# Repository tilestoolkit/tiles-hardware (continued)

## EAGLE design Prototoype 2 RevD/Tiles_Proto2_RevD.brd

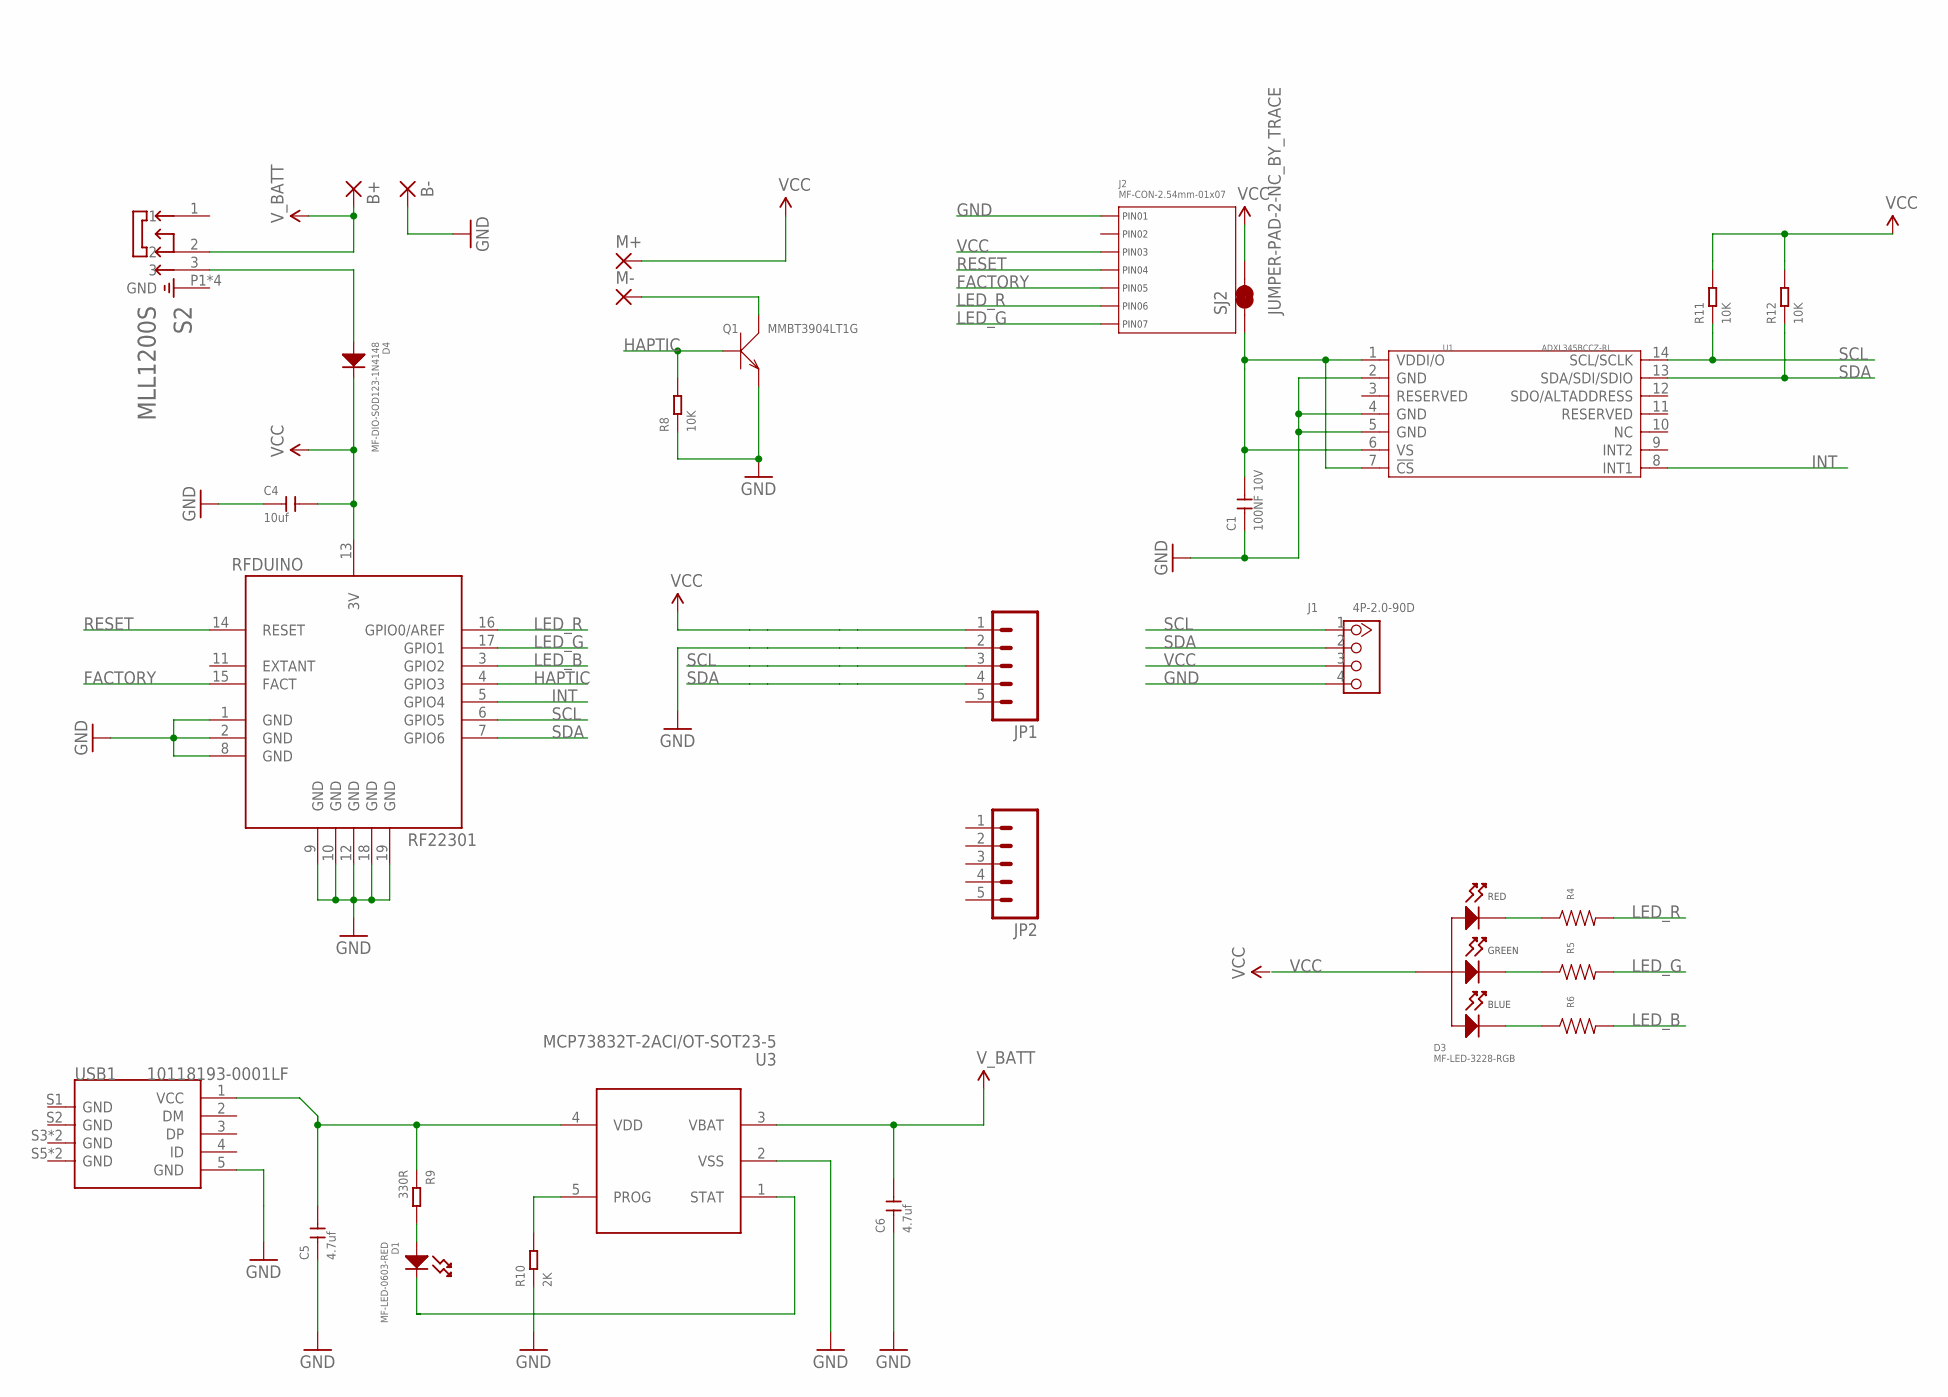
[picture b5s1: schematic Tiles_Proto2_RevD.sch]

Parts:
B+: SMD2; SMD1,27-2,54
B-: SMD2; SMD1,27-2,54
C1: 100NF 10V; C0402
C4: 10uf; C0402
C5, C6: 4.7uf; C0402
D1: MF-LED-0603-RED; LED0603
D3: MF-LED-3228-RGB; PLCC4
D4: MF-DIO-SOD123-1N4148; SOD-123
J1: 4P-2.0-90D; HW4-2.0-90D
J2: MF-CON-2.54mm-01x07; PTH_2.54MM_01X07
JP1, JP2: M05PTH; 1X05
M+: SMD2; SMD1,27-2,54
M-: SMD2; SMD1,27-2,54
Q1: MMBT3904LT1G; SOT-23
R4, R5, R6: RESISTOR_0603; R0603
R8, R11, R12: 10K; R0603
R9: 330R; R0603
R10: 2K; R0603
RFDUINO: RF22301; RFD22301
S2: MLL1200S; SW_MLL1200S
SJ2: JUMPER-PAD-2-NC_BY_TRACE; PAD-JUMPER-2-NC_BY_TRACE_YES_SILK
U1: ADXL345BCCZ-RL; LGA14-0.8-5.0X3.0MM
U3: MCP73832T-2ACI/OT-SOT23-5; SOT-23-5
USB1: 10118193-0001LF; MICRO-USB5+6P-SMD-0.65-B

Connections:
FACTORY: J2.P$5 (PIN5), RFDUINO.15 (FACT)
GND: B-.1, C1.1, C4.1, C5.1, C6.1, J1.4, J2.P$1 (PIN1), JP1.2, Q1.2 (E), R8.1, R10.1, RFDUINO.1 (GND), RFDUINO.2 (GND), RFDUINO.8 (GND), RFDUINO.9 (GND), RFDUINO.10 (GND), RFDUINO.12 (GND), RFDUINO.18 (GND), RFDUINO.19 (GND), S2.P1 (GND), S2.P2 (GND), S2.P3 (GND), S2.P4 (GND), U1.2 (GND), U1.4 (GND), U1.5 (GND), U3.2 (VSS), USB1.5 (GND)
HAPTIC: Q1.1 (B), R8.2, RFDUINO.4 (GPIO3)
INT: RFDUINO.5 (GPIO4), U1.8 (INT1)
LED_B: R6.P$2, RFDUINO.3 (GPIO2)
LED_G: J2.P$7 (PIN7), R5.P$2, RFDUINO.17 (GPIO1)
LED_R: J2.P$6 (PIN6), R4.P$2, RFDUINO.16 (GPIO0/AREF)
unnamed: D3.P$2 (CATHODE_RED), R4.P$1
unnamed: D3.P$3 (CATHODE_GREEN), R5.P$1
unnamed: M-.1, Q1.3 (C)
unnamed: C5.2, R9.1, U3.4 (VDD), USB1.1 (VCC)
unnamed: D4.ANODE, S2.3
unnamed: D1.ANODE, R9.2
unnamed: D1.CATHODE, U3.1 (STAT)
unnamed: R10.2, U3.5 (PROG)
unnamed: D3.P$4 (CATHODE_BLUE), R6.P$1
RESET: J2.P$4 (PIN4), RFDUINO.14 (RESET)
SCL: J1.1, JP1.3, R11.1, RFDUINO.6 (GPIO5), U1.14 (SCL/SCLK)
SDA: J1.2, JP1.4, R12.1, RFDUINO.7 (GPIO6), U1.13 (SDA/SDI/SDIO)
VCC: C4.2, D3.P$1 (ANODE), D4.CATHODE, J1.3, J2.P$3 (PIN3), JP1.1, M+.1, R11.2, R12.2, RFDUINO.13 (3V), SJ2.2
VDDI/O: C1.2, SJ2.1, U1.1 (VDDI/O), U1.6 (VS), U1.7 (!CS)
V_BATT: B+.1, C6.2, S2.2, U3.3 (VBAT)

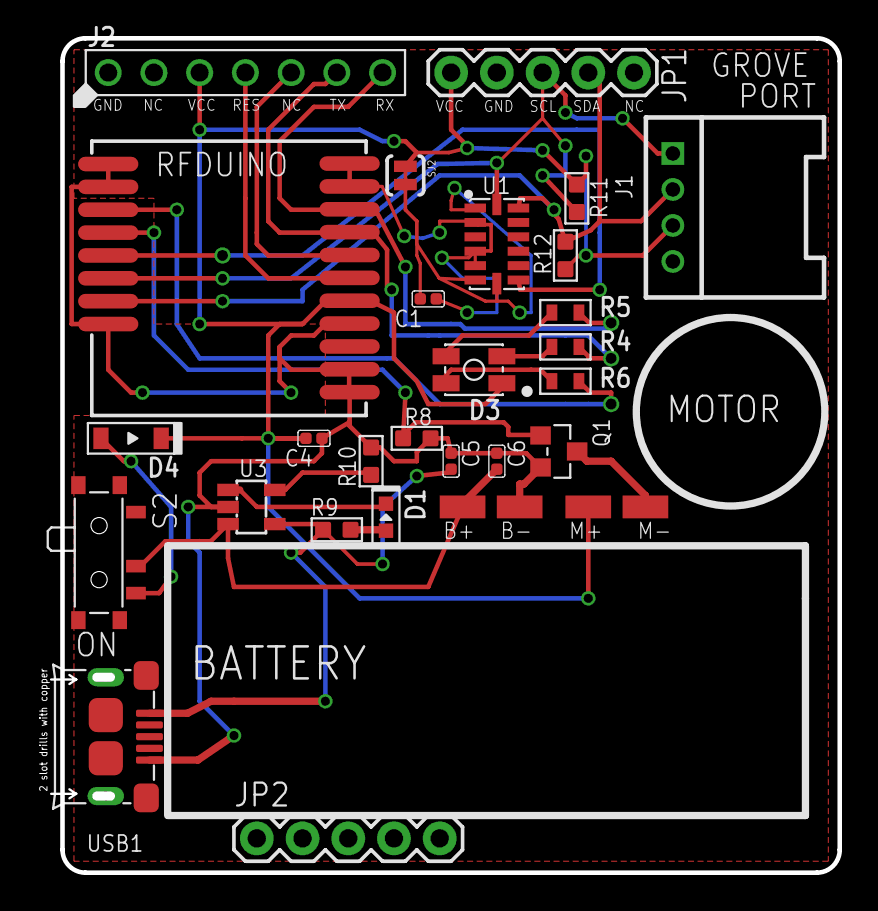
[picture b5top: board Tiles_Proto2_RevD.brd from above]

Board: 2 copper layers, 43.8 x 46.4 mm, 30 parts (0 on the bottom side), 22 nets.

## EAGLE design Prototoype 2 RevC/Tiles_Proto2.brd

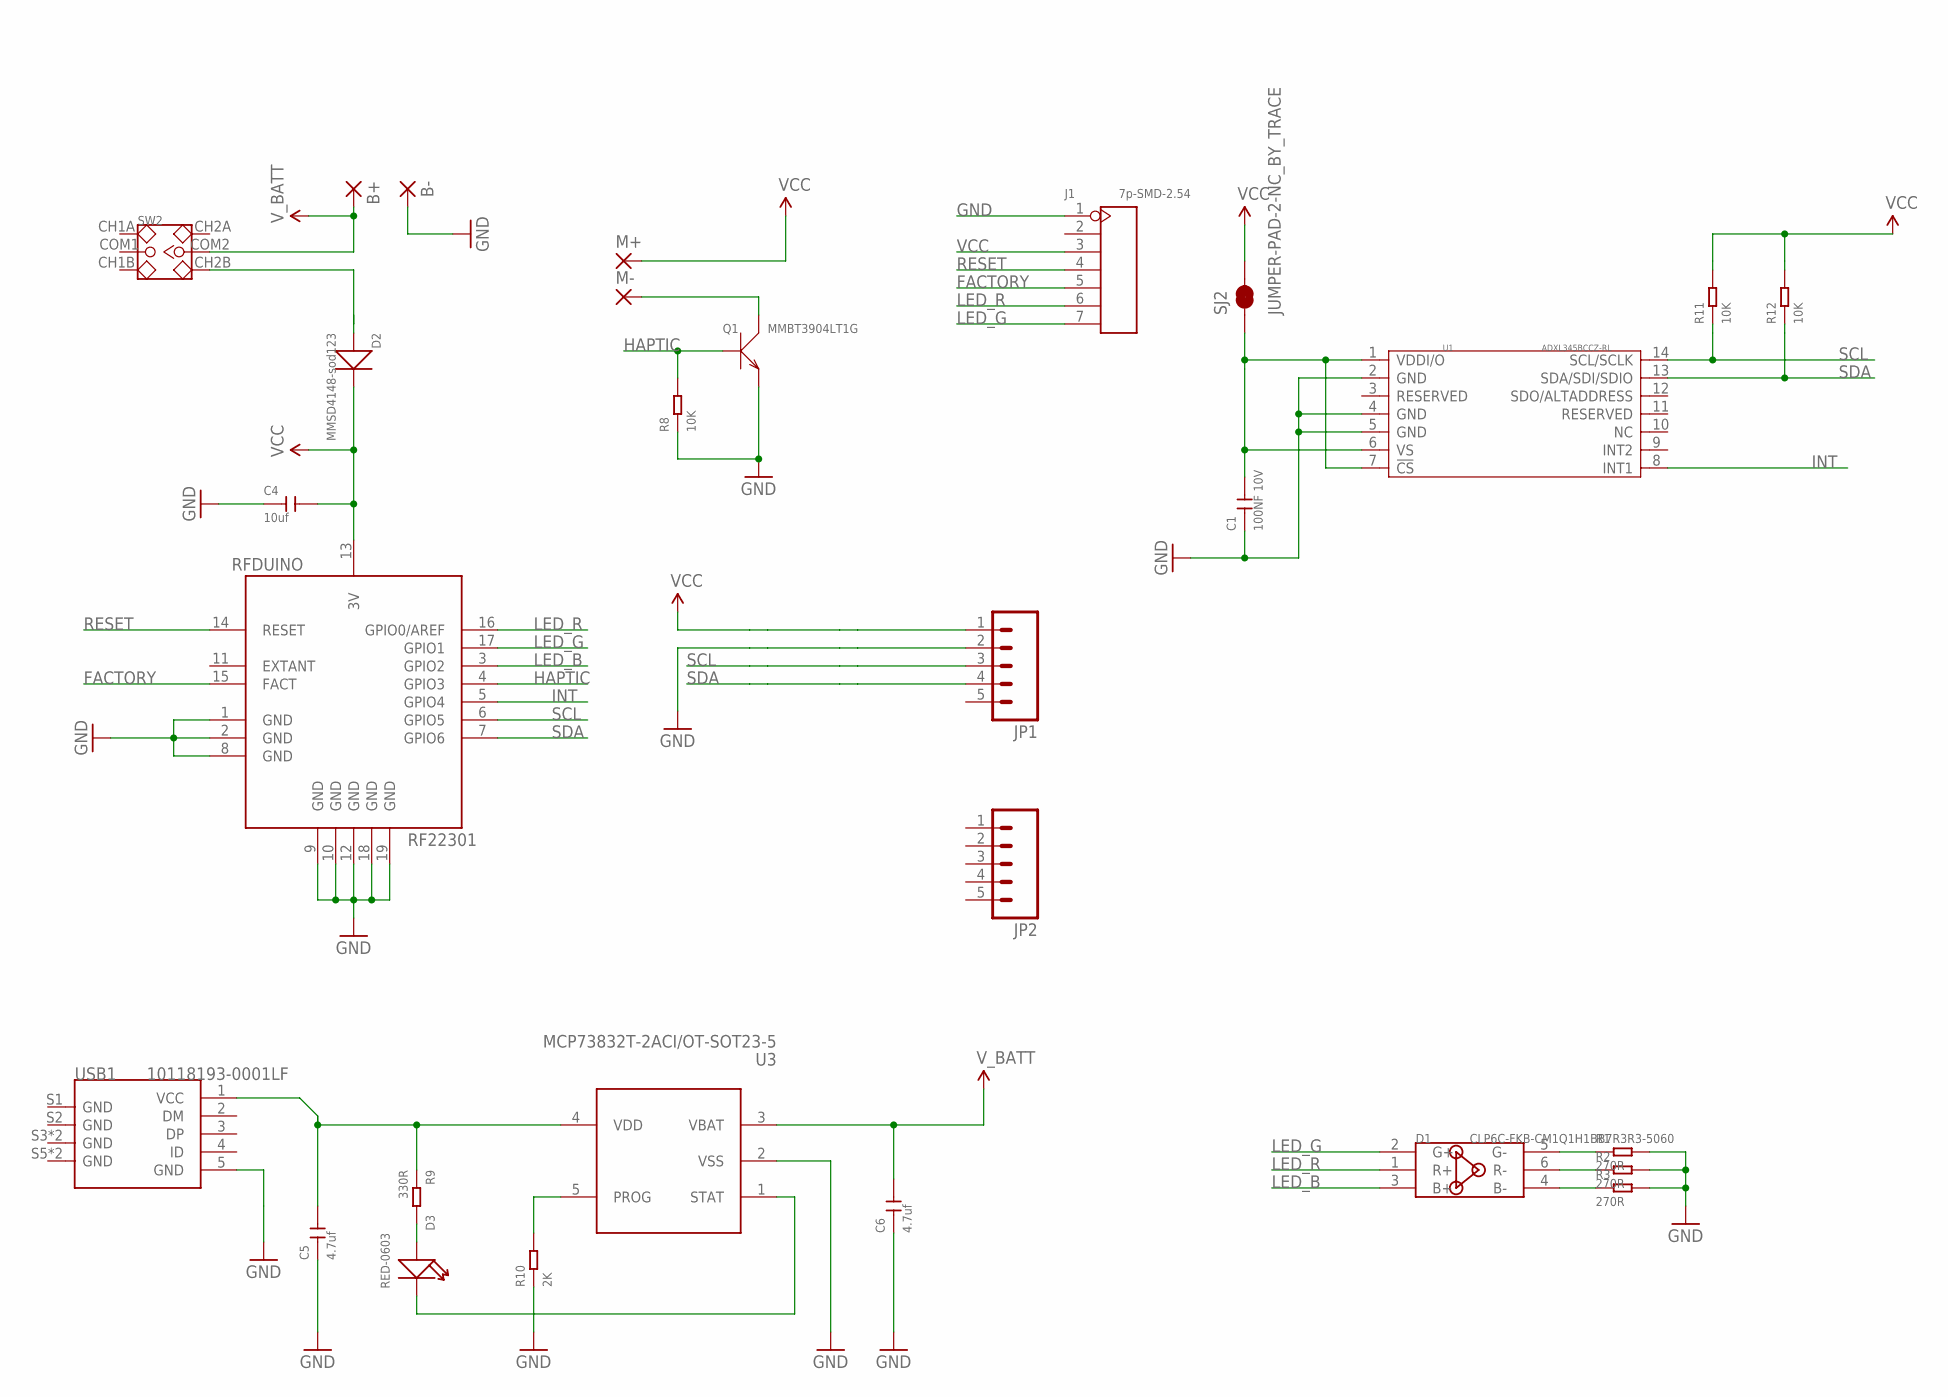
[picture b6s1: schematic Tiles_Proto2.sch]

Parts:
B+: SMD2; SMD1,27-2,54
B-: SMD2; SMD1,27-2,54
C1: 100NF 10V; C0402
C4: 10uf; C0402
C5, C6: 4.7uf; C0402
D1: CLP6C-FKB-CM1Q1H1BB7R3R3-5060; LED6-SMD-5060
D2: MMSD4148-sod123; SOD-123
D3: RED-0603; LED-0603
J1: 7p-SMD-2.54; H7-SMD-2.54
JP1, JP2: M05PTH; 1X05
M+: SMD2; SMD1,27-2,54
M-: SMD2; SMD1,27-2,54
Q1: MMBT3904LT1G; SOT-23
R1, R2, R3: 270R; R0805
R8, R11, R12: 10K; R0603
R9: 330R; R0603
R10: 2K; R0603
RFDUINO: RF22301; RFD22301
SJ2: JUMPER-PAD-2-NC_BY_TRACE; PAD-JUMPER-2-NC_BY_TRACE_YES_SILK
SW2: DIP-TOGGLE-SWITCH-2CH-(2X3P-2.54-90D)'90D'; SW6-2.54-9.0X3.5X3.2MM-90D
U1: ADXL345BCCZ-RL; LGA14-0.8-5.0X3.0MM
U3: MCP73832T-2ACI/OT-SOT23-5; SOT-23-5
USB1: 10118193-0001LF; MICRO-USB5+6P-SMD-0.65-B

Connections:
FACTORY: J1.5, RFDUINO.15 (FACT)
GND: B-.1, C1.1, C4.1, C5.1, C6.1, J1.1, JP1.2, Q1.2 (E), R1.2, R2.2, R3.2, R8.1, R10.1, RFDUINO.1 (GND), RFDUINO.2 (GND), RFDUINO.8 (GND), RFDUINO.9 (GND), RFDUINO.10 (GND), RFDUINO.12 (GND), RFDUINO.18 (GND), RFDUINO.19 (GND), U1.2 (GND), U1.4 (GND), U1.5 (GND), U3.2 (VSS), USB1.5 (GND)
HAPTIC: Q1.1 (B), R8.2, RFDUINO.4 (GPIO3)
INT: RFDUINO.5 (GPIO4), U1.8 (INT1)
LED_B: D1.3 (B+), RFDUINO.3 (GPIO2)
LED_G: D1.2 (G+), J1.7, RFDUINO.17 (GPIO1)
LED_R: D1.1 (R+), J1.6, RFDUINO.16 (GPIO0/AREF)
unnamed: D1.5 (G-), R1.1
unnamed: D1.6 (R-), R2.1
unnamed: D1.4 (B-), R3.1
unnamed: M-.1, Q1.3 (C)
unnamed: C5.2, R9.1, U3.4 (VDD), USB1.1 (VCC)
unnamed: D2.+, SW2.CH2B
unnamed: D3.+, R9.2
unnamed: D3.-, U3.1 (STAT)
unnamed: R10.2, U3.5 (PROG)
RESET: J1.4, RFDUINO.14 (RESET)
SCL: JP1.3, R11.1, RFDUINO.6 (GPIO5), U1.14 (SCL/SCLK)
SDA: JP1.4, R12.1, RFDUINO.7 (GPIO6), U1.13 (SDA/SDI/SDIO)
VCC: C4.2, D2.-, J1.3, JP1.1, M+.1, R11.2, R12.2, RFDUINO.13 (3V), SJ2.2
VDDI/O: C1.2, SJ2.1, U1.1 (VDDI/O), U1.6 (VS), U1.7 (!CS)
V_BATT: B+.1, C6.2, SW2.COM2, U3.3 (VBAT)

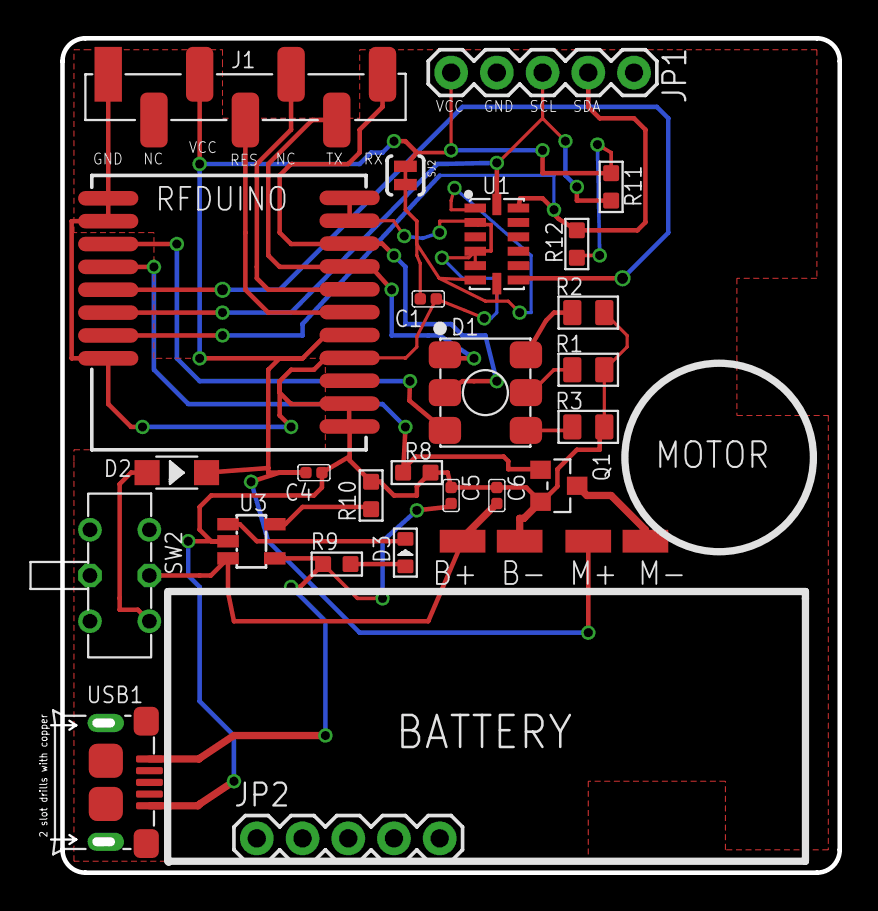
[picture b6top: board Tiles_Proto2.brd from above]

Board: 2 copper layers, 43.8 x 46.4 mm, 29 parts (0 on the bottom side), 22 nets.

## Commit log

2015-11-05 Tiles SCH first draft
2015-11-05 first draft board
2015-11-09 version before starting routing
2015-11-09 routing in progress
2015-11-17 finished routing, no silk screen
2015-11-17 top silskreen
2015-11-17 finished silkscreen, no copper pour
2015-11-18 ready for submission
2015-11-18 added BOM
2015-11-19 fixed 6 pins header
2015-11-20 before copper pour
2015-11-20 ready for production
2016-02-12 Start of Proto2RevB
2016-11-30 refactoring
2017-01-02 added license details
2017-01-20 added imgs
2017-01-20 firmware initial commit
2017-02-03 minor fixes
2017-02-03 added platformio IDE compatibility
2017-02-03 minor fix
2017-02-05 added LED brightness variable
2017-02-05 changed license details
2017-02-05 unused functions deleted
2017-03-15 upgraded to eagle 8
2017-03-15 added tiles printer code
2017-03-22 added LED extension
2017-03-22 LED extension working copy
2017-04-06 added tiles printer construction box
2017-04-06 updated to eagle 8
2017-04-25 fw beta
2017-05-06 added pics square LED extension
2017-05-06 prototype 3 hw initiated
2017-05-06 fixed problem w comma separated values
2017-05-06 fixed common cathode issue
2017-05-06 disabled tilt and shake events
2017-05-18 boilerplate code created
2017-05-18 proto#3 schematics created
2017-05-18 added feedbacks
2017-05-18 encapsulated LED logic
2017-05-22 added primitive info to square extension fw
2017-05-22 routing finshed
2017-05-22 finished cleanup
2017-05-22 added text
2017-05-23 finished silkscreen
2017-05-23 silkscreen update
2017-05-24 added tiles dock
2017-05-24 increased holes to 3mm
2017-05-24 candidate p3 and dock
2017-05-25 dock and p3 ready for production
2017-05-26 p3 and dock ready for production
2017-05-26 added neostripclass
2017-05-26 switched imu from LSM9DS1 to ADXL345
2017-05-29 p3rA and dock p1rA sent to production
2017-05-29 updated bom
2017-08-13 eagle imgs import
2017-09-05 boilerplate code moved to a new repo
2017-09-05 splitted out fw dirs into a new repo
2017-09-26 removed firmware code
2017-10-04 BOM update
2017-11-14 added proto 3 Rev B
2017-11-16 finished placing proto3revB
2017-11-16 partial routing
2017-11-17 ready for prod
2017-11-20 added dock p1rb
2017-11-20 values back in sch
2017-11-21 re-added part values
2017-11-21 ready for ready for prod
2017-11-22 sent to production
2017-11-22 dock ready for prod
2017-12-11 cleanup
